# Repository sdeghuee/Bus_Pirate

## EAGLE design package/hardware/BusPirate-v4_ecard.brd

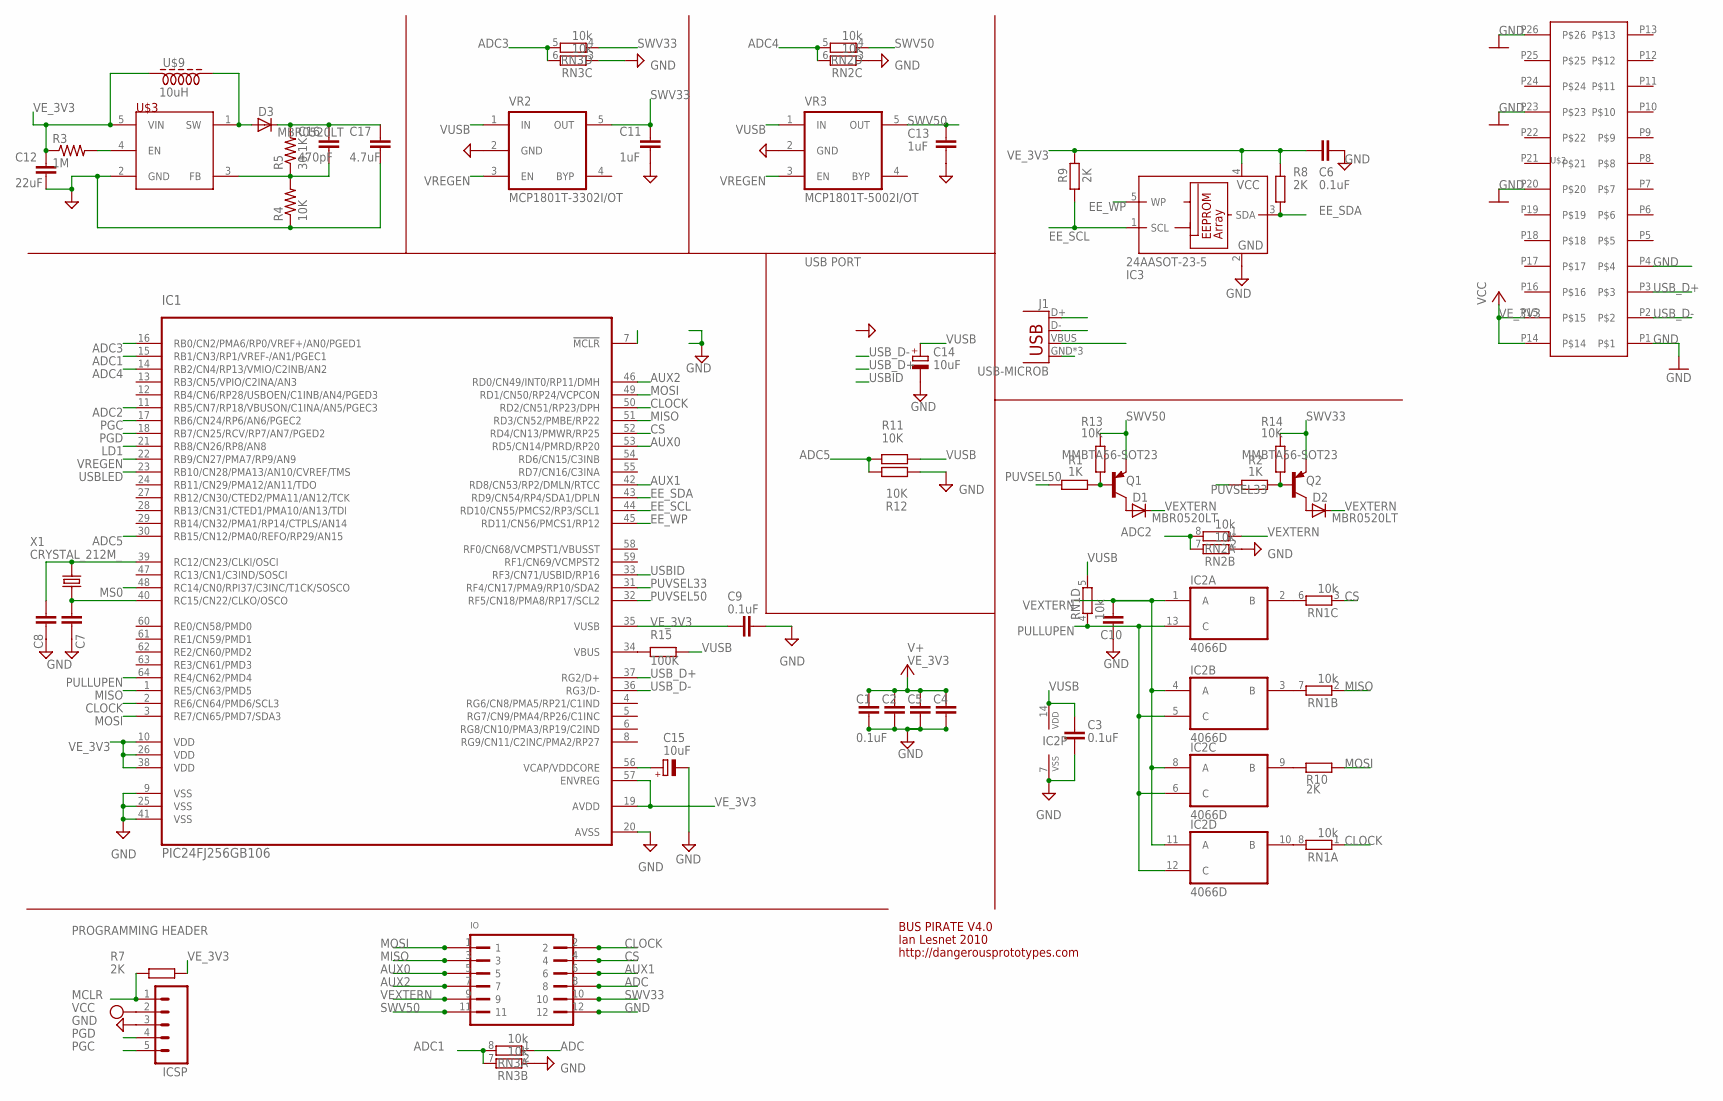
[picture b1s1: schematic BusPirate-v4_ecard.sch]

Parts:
C1, C2, C3, C4, C5, C6, C9, C10: 0.1uF; C0603
C7, C8: 27pF; C0603
C11, C13: 1uF; C0603
C12: 22uF; C0603
C14, C15: 10uF; SMC_A
C16: 470pF; C0603
C17: 4.7uF; C0603
D1, D2, D3: MBR0520LT; SOD123
IC1: PIC24FJ256GB106; TQFP64-10X10
IC2: 4066D; SO14
IC3: 24AASOT-23-5; SOT-23-5
ICSP: ICSP; 1X05
IO: PINSHRD-PTH-2X06; PINSHRD_PTH_2X06
J1: USB-MICROB
Q1, Q2: MMBTA56-SOT23; SOT23
R1, R2: 1K; R0603
R3: 1M; R0603
R4, R11, R12, R13, R14: 10K; R0603
R5: 30.1K; R0603
R7, R8, R9, R10: 2K; R0603
R15: 100K; R0603
RN1, RN2, RN3: 10k; RN8P-4R-CRA06S
U$2: EXPRESSCARD; EXPRESSCARD_EXPRESSCARD_PACK
U$3: LMR62421; SOT23-DBV
U$9: 10uH; 2520(1008)
VR2: MCP1801T-3302I/OT; SOT-23-5
VR3: MCP1801T-5002I/OT; SOT-23-5
X1: CRYSTAL_212M_; 4X6

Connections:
ADC: IO.8, RN3.1
ADC1: IC1.15 (RB1/CN3/RP1/VREF-/AN1/PGEC1), RN3.7 (2), RN3.8 (2)
ADC2: IC1.11 (RB5/CN7/RP18/VBUSON/C1INA/AN5/PGEC3), RN2.7 (2), RN2.8 (2)
ADC3: IC1.16 (RB0/CN2/PMA6/RP0/VREF+/AN0/PGED1), RN3.5 (2), RN3.6 (2)
ADC4: IC1.14 (RB2/CN4/RP13/VMIO/C2INB/AN2), RN2.5 (2), RN2.6 (2)
ADC5: IC1.30 (RB15/CN12/PMA0/REFO/RP29/AN15), R11.2, R12.2
AUX0: IC1.53 (RD5/CN14/PMRD/RP20), IO.5
AUX1: IC1.42 (RD8/CN53/RP2/DMLN/RTCC), IO.6
AUX2: IC1.46 (RD0/CN49/INT0/RP11/DMH), IO.7
CLOCK: IC1.2 (RE6/CN64/PMD6/SCL3), IC1.50 (RD2/CN51/RP23/DPH), IO.2, RN1.1
CS: IC1.52 (RD4/CN13/PMWR/RP25), IO.4, RN1.3 (1)
EE_SCL: IC1.44 (RD10/CN55/PMCS2/RP3/SCL1), IC3.1 (SCL), R9.1
EE_SDA: IC1.43 (RD9/CN54/RP4/SDA1/DPLN), IC3.3 (SDA), R8.1
EE_WP: IC1.45 (RD11/CN56/PMCS1/RP12), IC3.5 (WP)
GND: C1.2, C2.2, C3.2, C4.2, C5.2, C6.2, C7.2, C8.2, C9.2, C10.2, C11.2, C12.2, C13.2, C14.-, C15.-, C17.2, IC1.9 (VSS), IC1.20 (AVSS), IC1.25 (VSS), IC1.41 (VSS), IC2.7 (VSS), IC3.2 (GND), ICSP.3, IO.12, J1.GND, J1.MT1 (GND), J1.MT2 (GND), R4.1, R12.1, RN2.2 (1), RN2.3 (1), RN3.2 (1), RN3.3 (1), U$2.P1, U$2.P4, U$2.P20, U$2.P23, U$2.P26, U$3.2 (GND), VR2.2 (GND), VR3.2 (GND)
LD1: IC1.21 (RB8/CN26/RP8/AN8)
MCLR: IC1.7 (!MCLR), ICSP.1, R7.1
MISO: IC1.1 (RE5/CN63/PMD5), IC1.51 (RD3/CN52/PMBE/RP22), IO.3, RN1.2 (1)
MOSI: IC1.3 (RE7/CN65/PMD7/SDA3), IC1.49 (RD1/CN50/RP24/VCPCON), IO.1, R10.1
MS0: IC1.48 (RC14/CN0/RPI37/C3INC/T1CK/SOSCO)
unnamed: IC2.9 (B), R10.2
unnamed: IC2.10 (B), RN1.8 (2)
unnamed: D1.A, Q1.3 (C)
unnamed: IC2.2 (B), RN1.6 (2)
unnamed: IC2.3 (B), RN1.7 (2)
unnamed: D3.A, U$3.1 (SW), U$9.2
unnamed: R3.2, U$3.4 (EN)
unnamed: Q2.1 (B), R2.1, R14.2
unnamed: C7.1, IC1.40 (RC15/CN22/CLKO/OSCO), X1.2 (X2)
unnamed: C15.+, IC1.56 (VCAP/VDDCORE)
unnamed: IC1.34 (VBUS), R15.2
unnamed: C8.1, IC1.39 (RC12/CN23/CLKI/OSCI), X1.1 (X1)
unnamed: D2.A, Q2.3 (C)
unnamed: C16.2, R4.2, R5.1, U$3.3 (FB)
unnamed: Q1.1 (B), R1.1, R13.2
PGC: IC1.17 (RB6/CN24/RP6/AN6/PGEC2), ICSP.5
PGD: IC1.18 (RB7/CN25/RCV/RP7/AN7/PGED2), ICSP.4
PULLUPEN: IC1.64 (RE4/CN62/PMD4), IC2.5 (C), IC2.6 (C), IC2.12 (C), IC2.13 (C), RN1.4 (1)
PUVSEL33: IC1.31 (RF4/CN17/PMA9/RP10/SDA2), R2.2
PUVSEL50: IC1.32 (RF5/CN18/PMA8/RP17/SCL2), R1.2
SWV33: C11.1, IO.10, Q2.2 (E), R14.1, RN3.4 (1), VR2.5 (OUT)
SWV50: C13.1, IO.11, Q1.2 (E), R13.1, RN2.4 (1), VR3.5 (OUT)
USBID: IC1.33 (RF3/CN71/USBID/RP16)
USBLED: IC1.23 (RB10/CN28/PMA13/AN10/CVREF/TMS)
USB_D+: IC1.37 (RG2/D+), J1.D+, U$2.P3
USB_D-: IC1.36 (RG3/D-), J1.D-, U$2.P2
VEXTERN: C10.1, D1.C, D2.C, IC2.1 (A), IC2.4 (A), IC2.8 (A), IC2.11 (A), IO.9, RN2.1
VE_3V3: C1.1, C2.1, C4.1, C5.1, C6.1, C9.1, C12.1, IC1.10 (VDD), IC1.19 (AVDD), IC1.26 (VDD), IC1.35 (VUSB), IC1.38 (VDD), IC1.57 (ENVREG), IC3.4 (VCC), ICSP.2, R3.1, R7.2, R8.2, R9.2, U$2.P14, U$2.P15, U$3.5 (VIN), U$9.1
VREGEN: IC1.22 (RB9/CN27/PMA7/RP9/AN9), VR2.3 (EN), VR3.3 (EN)
VUSB: C3.1, C14.+, C16.1, C17.1, D3.C, IC2.14 (VDD), J1.VBUS, R5.2, R11.1, R15.1, RN1.5 (2), VR2.1 (IN), VR3.1 (IN)

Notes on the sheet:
PROGRAMMING HEADER
BUS PIRATE V4.0
Ian Lesnet 2010
http://dangerousprototypes.com
USB PORT

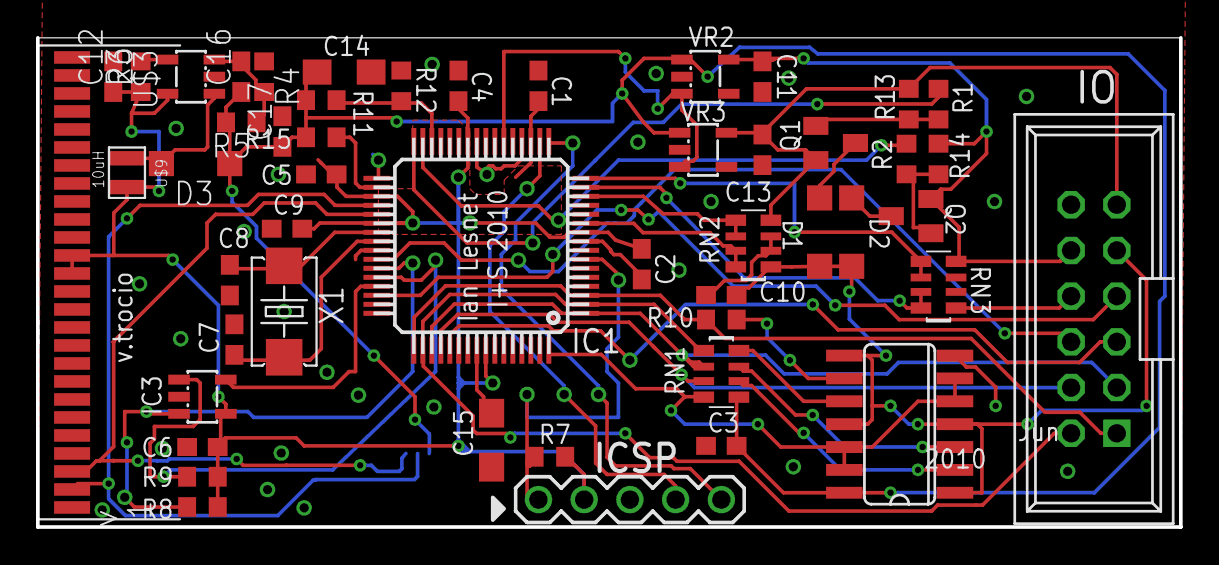
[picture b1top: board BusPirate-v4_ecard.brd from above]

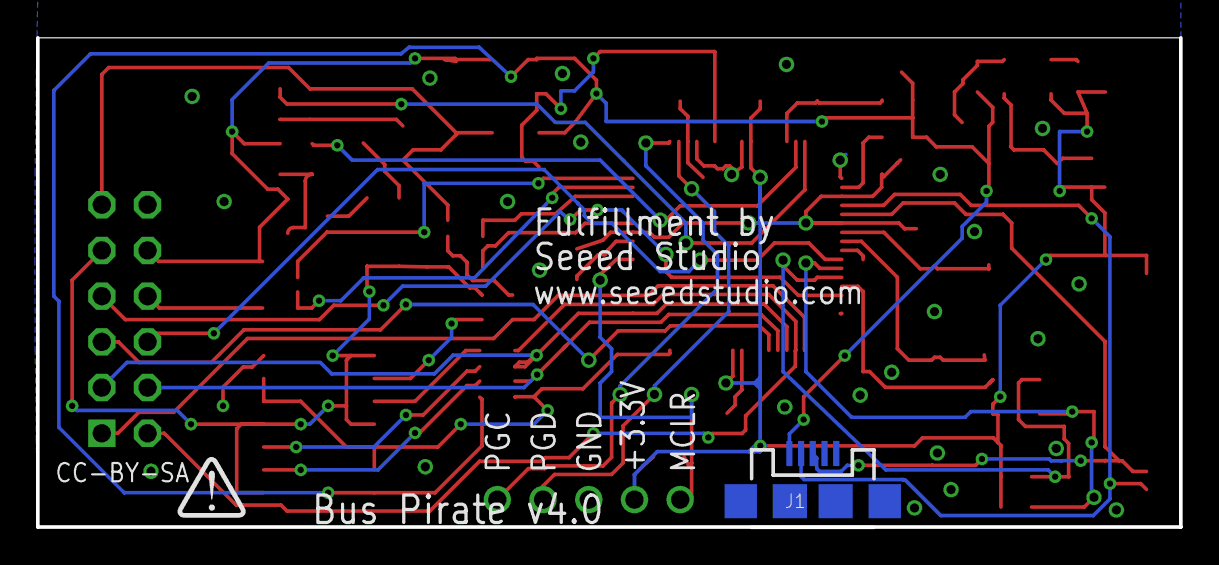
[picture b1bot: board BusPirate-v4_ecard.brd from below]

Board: 2 copper layers, 63.5 x 27.2 mm, 52 parts (2 on the bottom side), 46 nets.

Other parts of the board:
U$1: DP-LOGO

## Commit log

2017-11-21 update to add v4 hardware clone expresscard

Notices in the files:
package/hardware/BusPirate-v4_ecard.brd:
CC-BY-SA
parts and their libraries:
SparkFun-Connectors: Licensing: Creative Commons ShareAlike 4.0 International - https://creativecommons.org/licenses/by-sa/4.0
